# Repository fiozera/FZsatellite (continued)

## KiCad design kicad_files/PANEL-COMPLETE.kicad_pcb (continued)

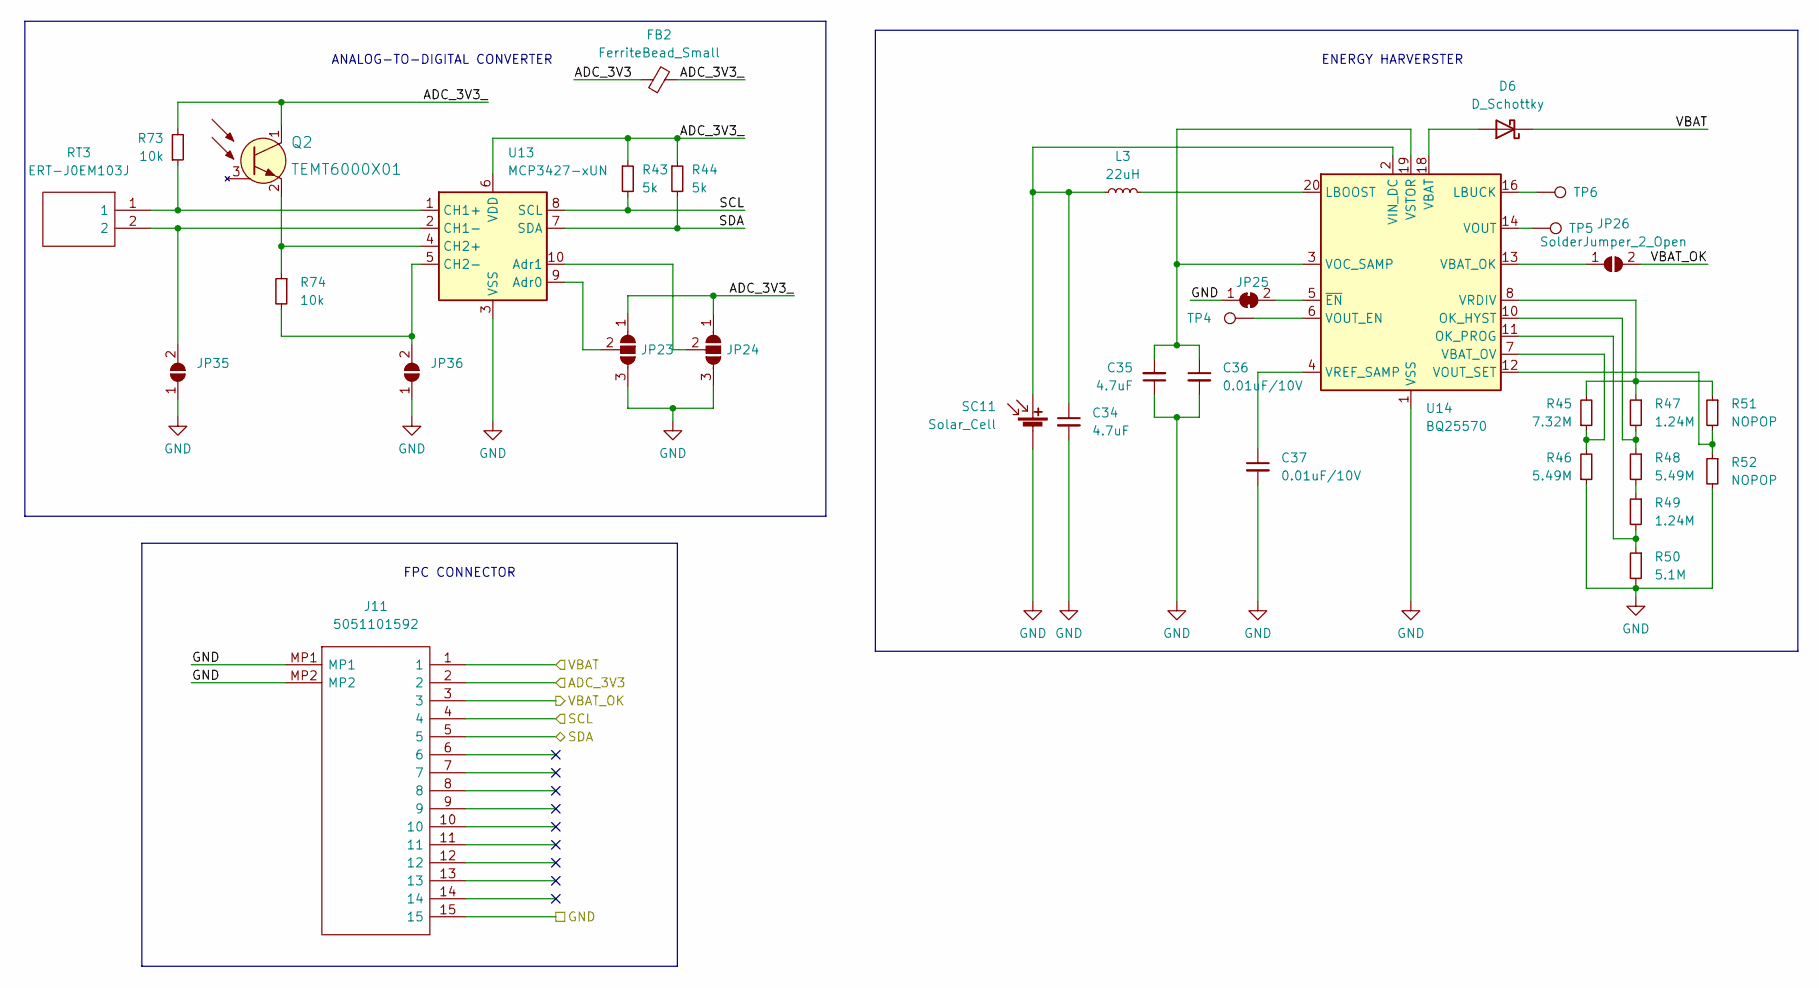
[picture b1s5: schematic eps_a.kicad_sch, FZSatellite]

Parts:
C34, C35: 4.7uF; C_0805_2012Metric
C36, C37: 0.01uF/10V; C_0402_1005Metric; Mouser Part 581-0402ZC103MAT2A
D6: D_Schottky; D_SOD-323
FB2: FerriteBead_Small; L_0603_1608Metric
J11: 5051101592; Manufacturer_Part_Number 5051101592
JP23, JP24: SolderJumper_3_Open; SolderJumper-3_P1.3mm_Open_RoundedPad1.0x1.5mm
JP25: SolderJumper_2_Bridged; SolderJumper-2_P1.3mm_Bridged_RoundedPad1.0x1.5mm
JP26, JP35, JP36: SolderJumper_2_Open; SolderJumper-2_P1.3mm_Open_RoundedPad1.0x1.5mm
L3: 22uH; LPS4018223MRC
Q2: TEMT6000X01; Phototransistor_SMD_4x2mm_TEMT6000X01; MPN TEMT6000X01; Digi-Key_PN 751-1055-1-ND
R43, R44: 5k; R_0402_1005Metric; Mouser Part 603-RC0402FR-075KL
R45: 7.32M; R_0402_1005Metric
R46, R48: 5.49M; R_0402_1005Metric
R47, R49: 1.24M; R_0402_1005Metric
R50: 5.1M; R_0402_1005Metric
R51, R52: NOPOP; R_0402_1005Metric
R73, R74: 10k; R_0603_1608Metric
RT3: ERT-J0EM103J; THRMC1005X55N; Mouser Part Number 667-ERT-J0EM103J
SC11: Solar_Cell; SM141K08LV
TP4, TP5, TP6: TestPoint; TestPoint_Pad_D1.0mm
U13: MCP3427-xUN; MSOP-10_3x3mm_P0.5mm
U14: BQ25570; QFN-20-1EP_3.5x3.5mm_P0.5mm_EP2x2mm

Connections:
/ADC_3V3: FB2.1, J11.2; also elsewhere on the board
/DEPNO: D6.1 (K), J11.1; also elsewhere on the board
/EPS A/ADC_3V3_: FB2.2, JP23.1 (A), JP24.1 (A), Q2.1 (C), R43.1, R44.1, R73.2, U13.6 (VDD)
/SCL1: J11.4, R43.2, U13.8 (SCL); also elsewhere on the board
/SDA1: J11.5, R44.2, U13.7 (SDA); also elsewhere on the board
/VBAT_OK: J11.3, JP26.2 (B); also elsewhere on the board
GND: C34.2, C35.1, C36.2, C37.2, J11.15, J11.MP1, J11.MP2, JP23.3 (B), JP24.3 (B), JP25.1 (A), JP35.1 (A), JP36.1 (A), R46.1, R50.2, R52.2, SC11.2 (-), U13.3 (VSS), U14.1 (VSS), U14.9 (VSS), U14.15 (VSS), U14.17 (VSS), U14.21 (VSS); also elsewhere on the board
unnamed: C34.1, L3.1, SC11.1 (+), U14.2 (VIN_DC)
unnamed: C35.2, C36.1, U14.3 (VOC_SAMP), U14.19 (VSTOR)
unnamed: C37.1, U14.4 (VREF_SAMP)
unnamed: D6.2 (A), U14.18 (VBAT)
unnamed: JP23.2 (C), U13.9 (Adr0)
unnamed: JP24.2 (C), U13.10 (Adr1)
unnamed: JP25.2 (B), U14.5 (~EN)
unnamed: JP26.1 (A), U14.13 (VBAT_OK)
unnamed: JP35.2 (B), RT3.2, U13.2 (CH1-)
unnamed: JP36.2 (B), R74.2, U13.5 (CH2-)
unnamed: L3.2, U14.20 (LBOOST)
unnamed: Q2.2 (E), R74.1, U13.4 (CH2+)
unnamed: R45.1, R46.2, U14.7 (VBAT_OV)
unnamed: R45.2, R47.1, R51.1, U14.8 (VRDIV)
unnamed: R47.2, R48.1, U14.10 (OK_HYST)
unnamed: R48.2, R49.1
unnamed: R49.2, R50.1, U14.11 (OK_PROG)
unnamed: R51.2, R52.1, U14.12 (VOUT_SET)
unnamed: R73.1, RT3.1, U13.1 (CH1+)
unnamed: TP4.1, U14.6 (VOUT_EN)
unnamed: TP5.1, U14.14 (VOUT)
unnamed: TP6.1, U14.16 (LBUCK)

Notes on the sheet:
ANALOG-TO-DIGITAL CONVERTER
FPC CONNECTOR
ENERGY HARVERSTER

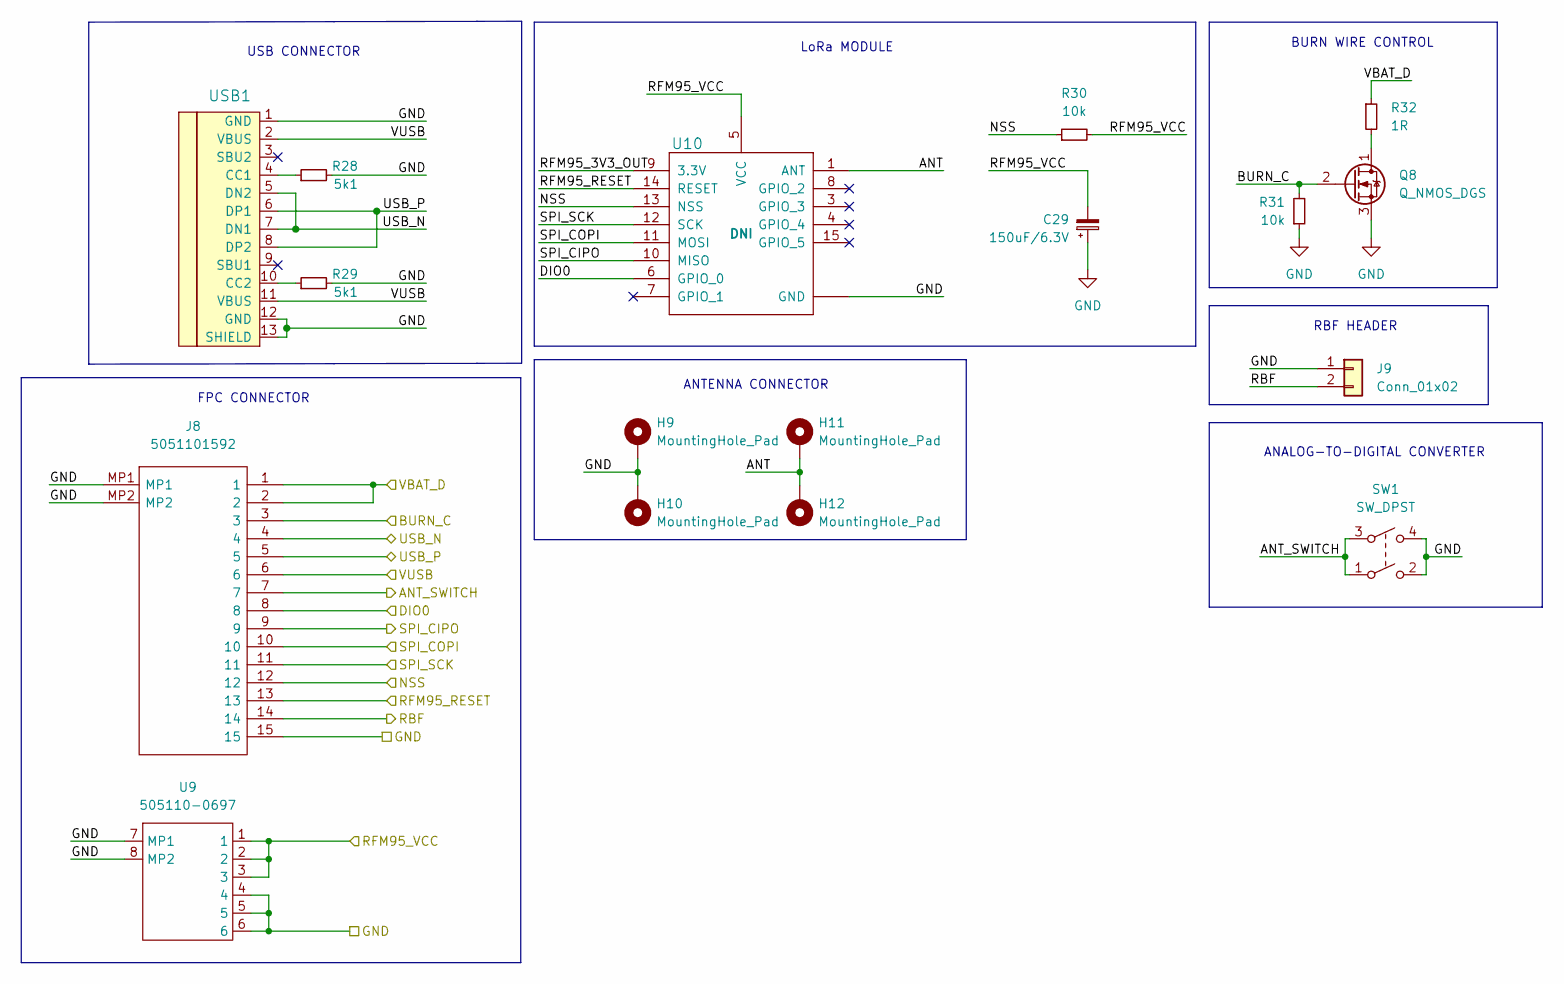
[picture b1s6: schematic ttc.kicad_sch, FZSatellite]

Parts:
C29: 150uF/6.3V; CP_EIA-7343-15_Kemet-W; Mouser Part 80-T520V157M006E025
H9, H10, H11, H12: MountingHole_Pad; MountingHole_2.2mm_M2_DIN965_Pad_TopOnly
J8: 5051101592; Manufacturer_Part_Number 5051101592
J9: Conn_01x02; PinHeader_1x02_P2.54mm_Horizontal
Q8: Q_NMOS_DGS; RUL035N02FRATR
R28, R29: 5k1; R_0603_1608Metric
R30, R31: 10k; R_0402_1005Metric
R32: 1R; R_Axial_DIN0207_L6.3mm_D2.5mm_P10.16mm_Horizontal
SW1: SW_DPST; SPPB530601
U9: 505110-0697; 5051100692
U10: RFM98PW; RFM95PW
USB1: HRO-TYPE-C-31-M-12; HRO-TYPE-C-31-M-12-HandSoldering

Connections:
/ANT_SWITCH: J8.7, SW1.1, SW1.3; also elsewhere on the board
/BURN_C: J8.3, Q8.2 (G), R31.2; also elsewhere on the board
/DIO0: J8.8, U10.6 (GPIO_0); also elsewhere on the board
/NSS: J8.12, R30.1, U10.13 (NSS); also elsewhere on the board
/RBF: J8.14, J9.2; also elsewhere on the board
/RFM95_RESET: J8.13, U10.14 (RESET); also elsewhere on the board
/RFM95_VCC: C29.2, R30.2, U9.1, U9.2, U9.3, U10.5 (VCC); also elsewhere on the board
/SPI_CIPO: J8.9, U10.10 (MISO); also elsewhere on the board
/SPI_COPI: J8.10, U10.11 (MOSI); also elsewhere on the board
/SPI_SCK: J8.11, U10.12 (SCK); also elsewhere on the board
/TTC/ANT: H11.1, H12.1, U10.1 (ANT)
/TTC/RFM95_3V3_OUT: U10.9 (3.3V)
/USB_N: J8.4, USB1.5 (DN2), USB1.7 (DN1); also elsewhere on the board
/USB_P: J8.5, USB1.6 (DP1), USB1.8 (DP2); also elsewhere on the board
/VBAT_D: J8.1, J8.2, R32.1; also elsewhere on the board
/VUSB: J8.6, USB1.2 (VBUS), USB1.11 (VBUS); also elsewhere on the board
GND: C29.1, H9.1, H10.1, J8.15, J8.MP1, J8.MP2, J9.1, Q8.3 (S), R28.2, R29.2, R31.1, SW1.2, SW1.4, U9.4, U9.5, U9.6, U9.7 (MP1), U9.8 (MP2), U10.2 (GND), U10.16 (GND), U10.17 (GND), USB1.1 (GND), USB1.12 (GND), USB1.13 (SHIELD); also elsewhere on the board
unnamed: Q8.1 (D), R32.2
unnamed: R28.1, USB1.4 (CC1)
unnamed: R29.1, USB1.10 (CC2)

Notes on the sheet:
ANALOG-TO-DIGITAL CONVERTER
BURN WIRE CONTROL
FPC CONNECTOR
RBF HEADER
USB CONNECTOR
LoRa MODULE
ANTENNA CONNECTOR

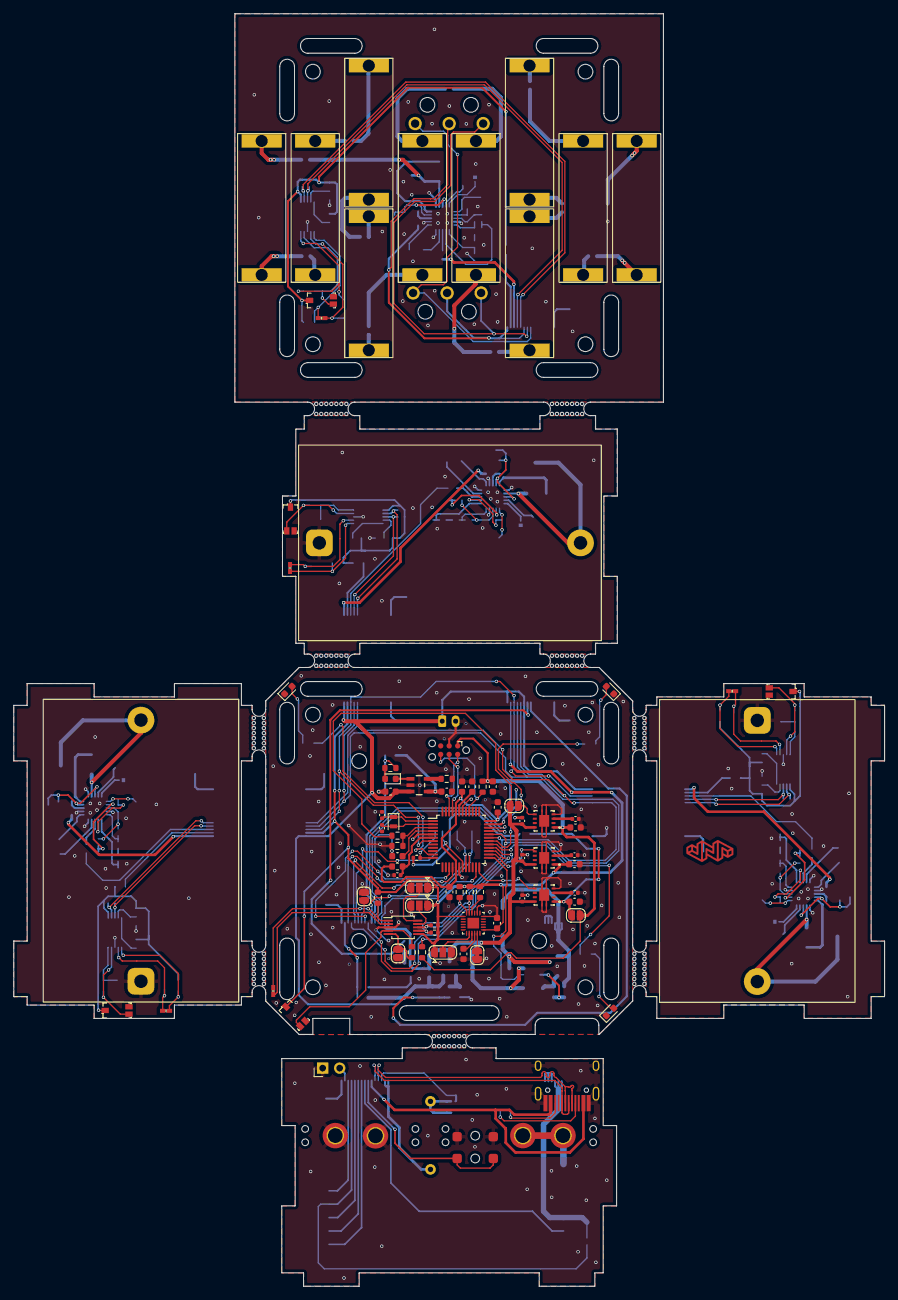
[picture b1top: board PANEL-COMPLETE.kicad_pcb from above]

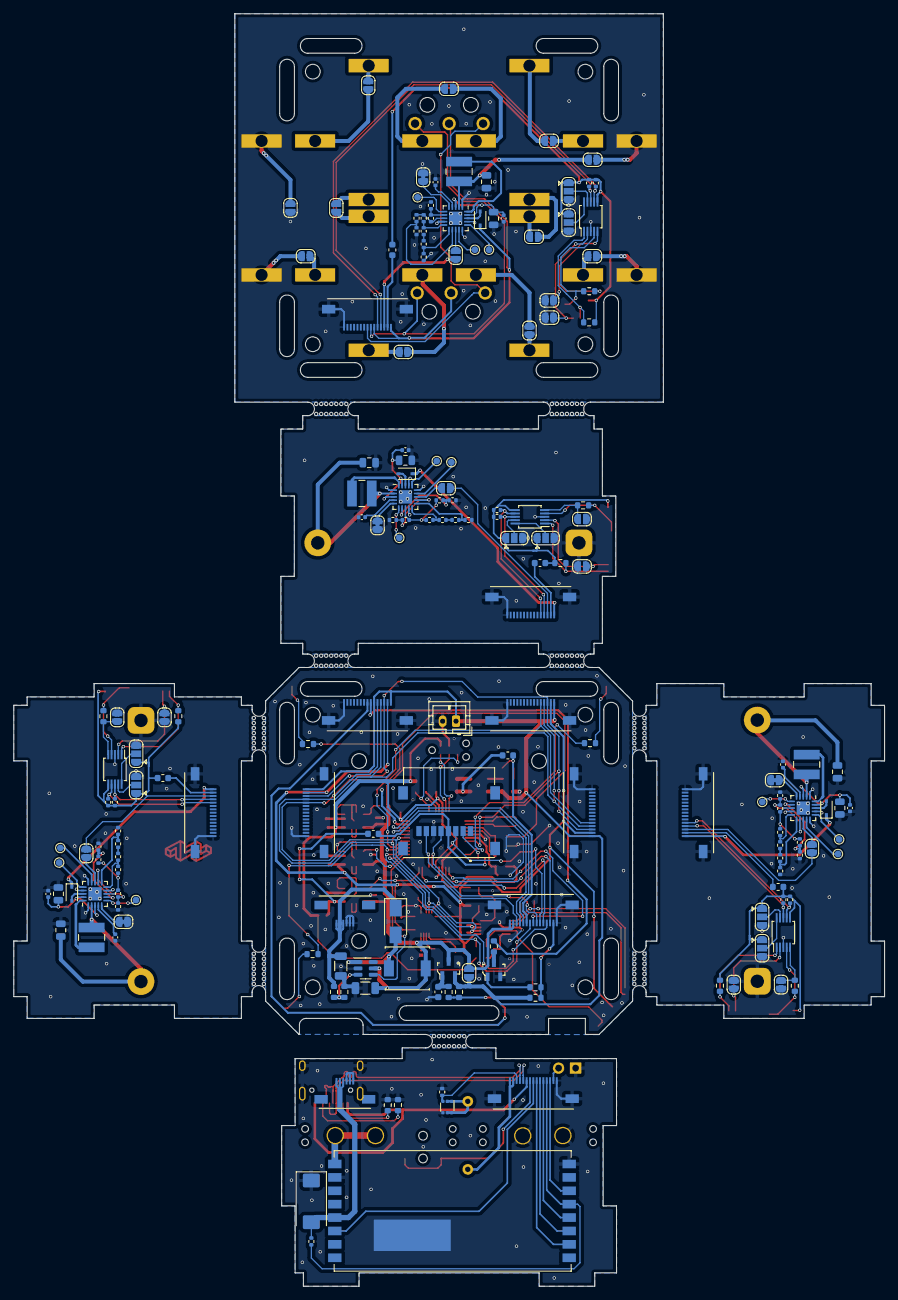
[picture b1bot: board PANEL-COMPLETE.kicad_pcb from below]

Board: 2 copper layers, 130.0 x 190.0 mm, 285 parts (173 on the bottom side), 183 nets.

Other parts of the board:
mouse-bite-2mm-slot, mouse-bite-2mm-slot#2, mouse-bite-2mm-slot#3, mouse-bite-2mm-slot#4, mouse-bite-2mm-slot#5, mouse-bite-2mm-slot#6, mouse-bite-2mm-slot#7, mouse-bite-2mm-slot#8, mouse-bite-2mm-slot#9: VAL**; mouse-bite-2mm-slot

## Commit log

2022-11-08 add 3d models
2022-11-09 add gerber and kicad project files
2022-11-09 update gerber files
2022-11-09 update kicad files
2022-11-14 add base station transceiver files
2022-12-25 update components values
2022-12-25 add schematics.pdf
